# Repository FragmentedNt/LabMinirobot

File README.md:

# What's this

* sn研でやってる子供向けLEGOロボットのソースとか回路とか機械とか

# 数増やしたいんだけど

1. CircuitCase/Case1_2_9V2.stlおよびCircuitCase/Cover3.ncdを印刷/切削
1. Circuit_v1/ にあるGコードで基板削ってはんだ付け
1. Arduino nanoを用意してminirobo_rmlab/minirobo_rmlab.inoを書き込み
1. SBDBT(3.3V/5V問わず)を用意する
1. MPLAB IPEで sbdbt_ps3_v4/sbxbt_ps3.X/dist/default/production/sbxbt_ps3.X.production.hexを書き込む
1. Done!

# 改善要望

* 回路ケースここまで大きくなくていい
  * LEGOポッチつけたのは大失敗なので消して適当なLEGO板貼り付けるのがベスト
* DCジャック，配線通してはんだ付けするのクソでは？
  * ほんまそれな
* TA8428Kがディスコン
  * 8SOICのイカした後継ICが出てるはず

# 連絡先

* fragmentednt@zoho.com

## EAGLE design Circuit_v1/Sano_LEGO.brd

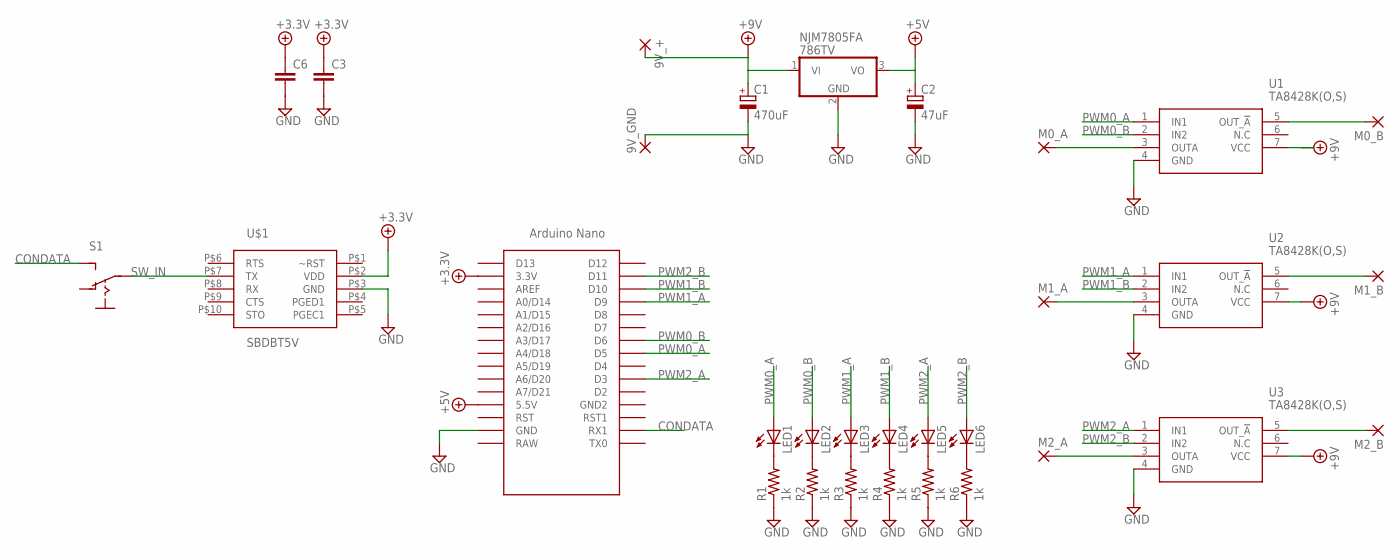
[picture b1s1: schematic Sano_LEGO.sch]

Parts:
9V_+, 9V_GND: 3,81/1,4
C1: 470uF; E3,5-10
C2: 47uF; E2-5
C3, C6: C-EU025-025X050; C025-025X050
LED1, LED2, LED3, LED4, LED5, LED6: LED3MM
M0_A, M0_B, M1_A, M1_B, M2_A, M2_B: 3,81/1,4
NJM7805FA: 786TV; TO220V
R1, R2, R3, R4, R5, R6: 1k; R1608
S1: S-SWITCHSMALL; DS
U1, U2, U3: TA8428K(O,S); HSIP7-P-2.54_1
U$1: SBDBT5V; SBDBT
U$2: NANO

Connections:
+3.3V: C3.1, C6.1, U$1.P$2 (VDD), U$2.3.3V
+5V: C2.+, NJM7805FA.3 (VO), U$2.5V (5.5V)
+9V: 9V_+.1, C1.+, NJM7805FA.1 (VI), U1.7 (VCC), U2.7 (VCC), U3.7 (VCC)
CONDATA: S1.P$3 (S), U$2.RX1
GND: 9V_GND.1, C1.-, C2.-, C3.2, C6.2, NJM7805FA.2 (GND), R1.1, R2.1, R3.1, R4.1, R5.1, R6.1, U1.4 (GND), U2.4 (GND), U3.4 (GND), U$1.P$3 (GND), U$2.GND
unnamed: LED1.K (C), R1.2
unnamed: M0_A.1, U1.3 (OUTA)
unnamed: M0_B.1, U1.5 (OUT_!A)
unnamed: M1_B.1, U2.5 (OUT_!A)
unnamed: M1_A.1, U2.3 (OUTA)
unnamed: M2_B.1, U3.5 (OUT_!A)
unnamed: M2_A.1, U3.3 (OUTA)
unnamed: LED2.K (C), R2.2
unnamed: LED3.K (C), R3.2
unnamed: LED4.K (C), R4.2
unnamed: LED5.K (C), R5.2
unnamed: LED6.K (C), R6.2
PWM0_A: LED1.A, U1.1 (IN1), U$2.D5
PWM0_B: LED2.A, U1.2 (IN2), U$2.D6
PWM1_A: LED3.A, U2.1 (IN1), U$2.D9
PWM1_B: LED4.A, U2.2 (IN2), U$2.D10
PWM2_A: LED5.A, U3.1 (IN1), U$2.D3
PWM2_B: LED6.A, U3.2 (IN2), U$2.D11
SW_IN: S1.P$2, U$1.P$7 (TX)

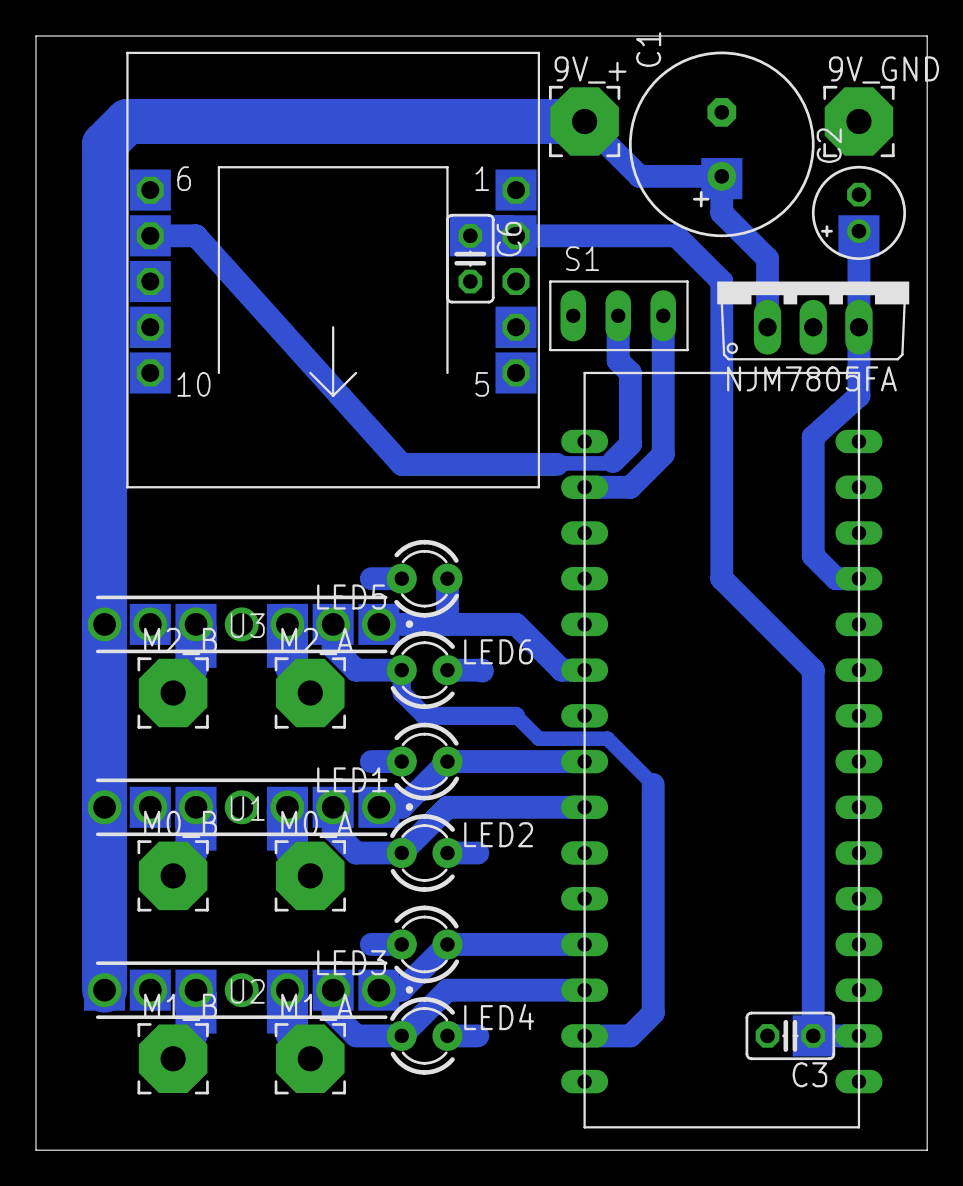
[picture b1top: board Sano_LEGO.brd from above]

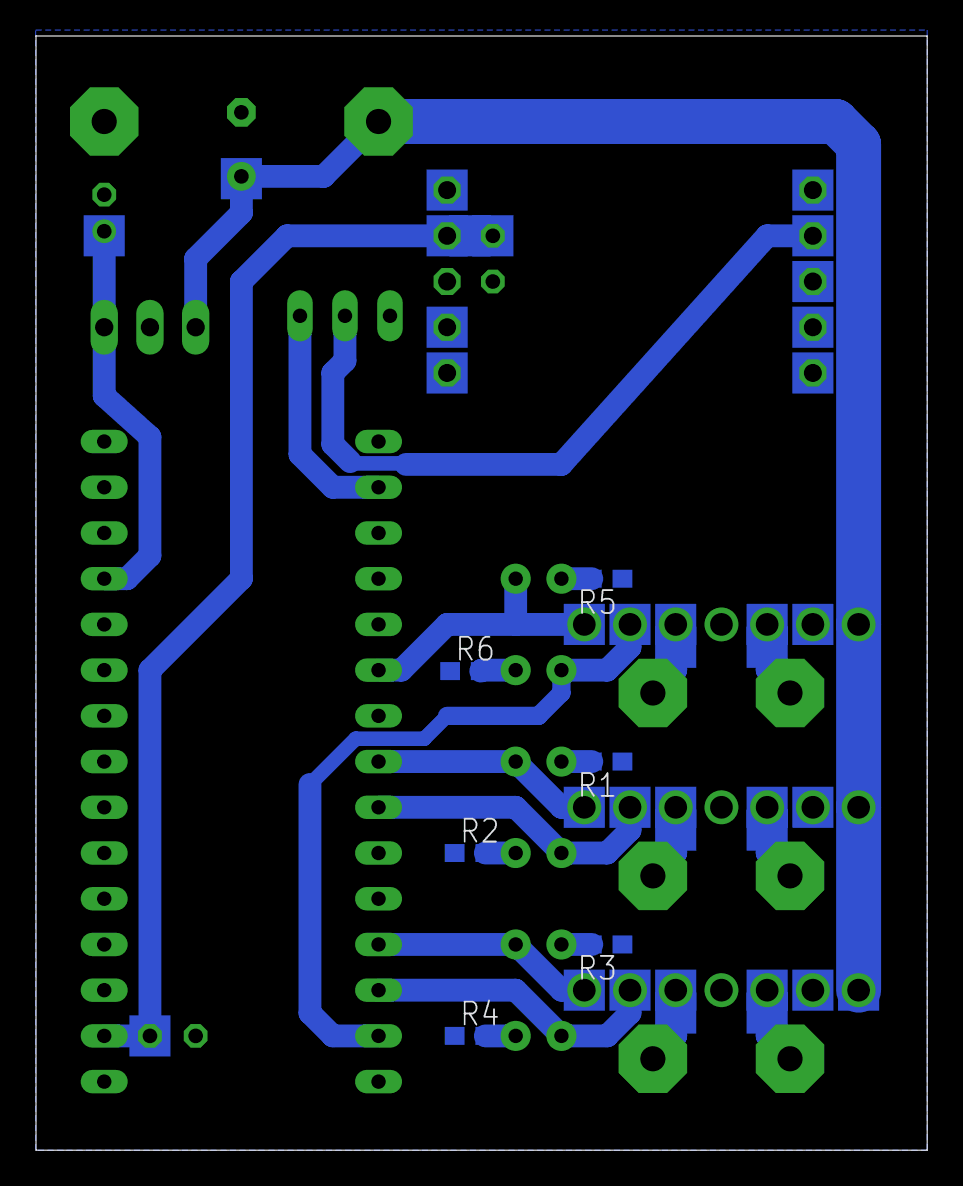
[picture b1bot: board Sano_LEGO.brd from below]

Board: 2 copper layers, 49.5 x 61.9 mm, 31 parts (6 on the bottom side), 24 nets.

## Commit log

2018-08-25 Copy from Arduino solution
2018-08-29 psconクラス作成
2018-08-29 PSコンの読み取り実装 動確は未だ duty，degree計算は未実装
2018-08-30 pscon周り修正
2018-08-30 モタドラ駆動クラスを追加
2018-09-02 add .gitignore
2018-09-02 .gitignore
2018-09-02 キャッシュを削除し.gitignoreの変更を反映
2018-09-02 Timer0を用いる標準関数をラップするクラスの作成 PWMの周波数を変更すると影響が出るため
2018-09-02 wiring.hを書き換えるほうが正しそうなのでTM0.h，TM0.cppを除外
2018-09-02 Revert "wiring.hを書き換えるほうが正しそうなのでTM0.h，TM0.cppを除外"
    This reverts commit 7ff5ff75d863093fb7d0a68c891945ebe1ebf533.
2018-09-02 PWM周波数変更
2018-09-02 delayMicrosecondはTimer0と無関係なことが判明したので変更 なお精度
2018-09-02 いろいろ
2018-09-03 PWM周波数変更 分周無しではモタドラICの挙動に変化が見られなかったため
2018-10-14 ディジタルピンモードを追加
2018-11-17 visual studioがなんかした感じ
2019-10-07 add: SBDBTのプロジェクトを追加
2019-10-07 update: 左スティック前進，右スティック旋回に変更
2019-10-08 update: 独立駆動2輪とモードチェンジができるように変更
2019-10-08 制御周期を20msにして正しくFallを取れるようにした
2019-10-09 update: MPLABがなんかやったっぽい
2019-10-09 add: 回路データ追加
2019-10-09 add: 回路ケースCADを追加（バイナリ含む）
2019-10-23 update: コメント追加してVisualStudio拡張用のファイル削除
2019-10-23 update: update Readme.md
2019-10-23 update: Readme.md
